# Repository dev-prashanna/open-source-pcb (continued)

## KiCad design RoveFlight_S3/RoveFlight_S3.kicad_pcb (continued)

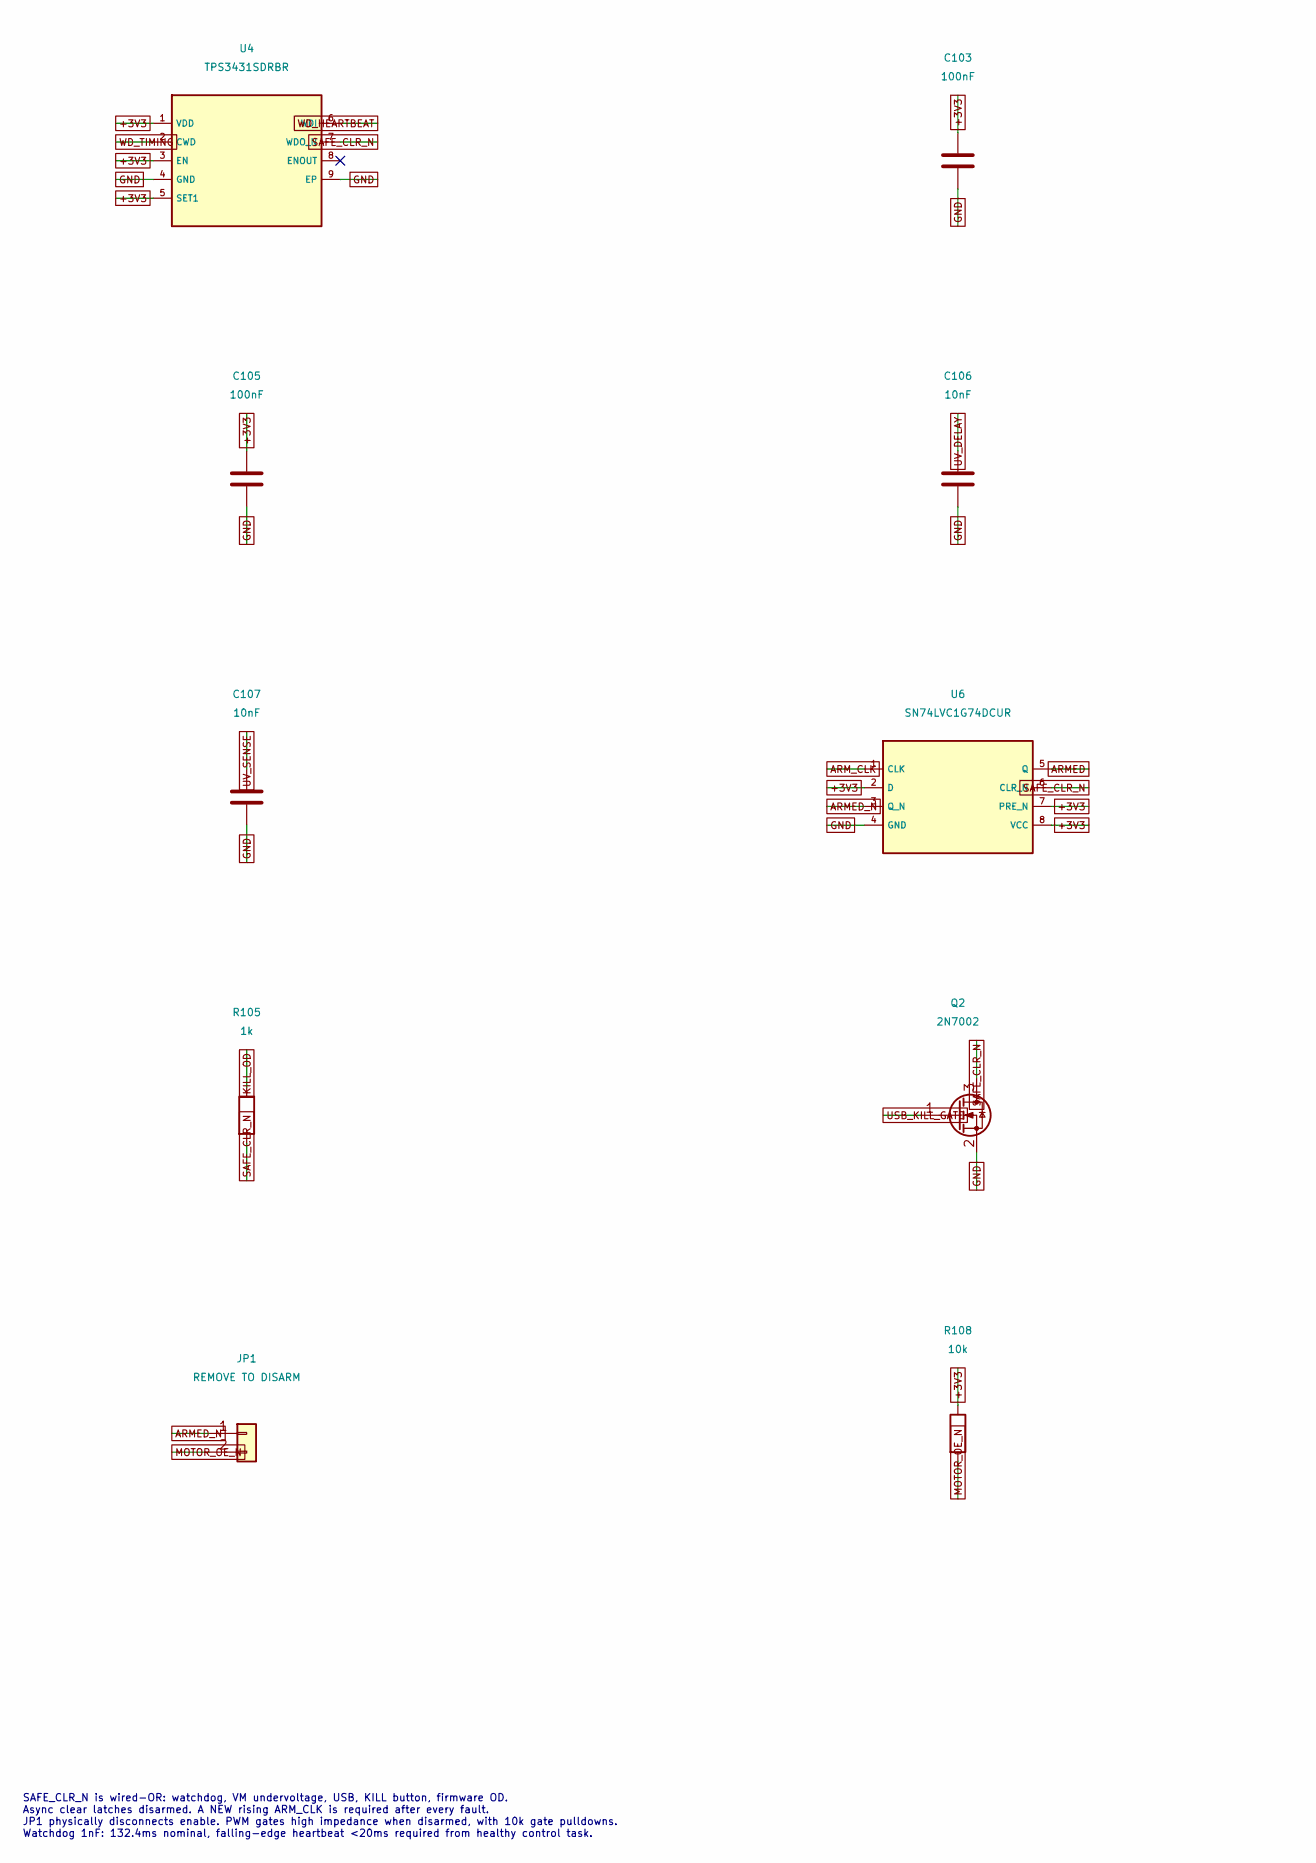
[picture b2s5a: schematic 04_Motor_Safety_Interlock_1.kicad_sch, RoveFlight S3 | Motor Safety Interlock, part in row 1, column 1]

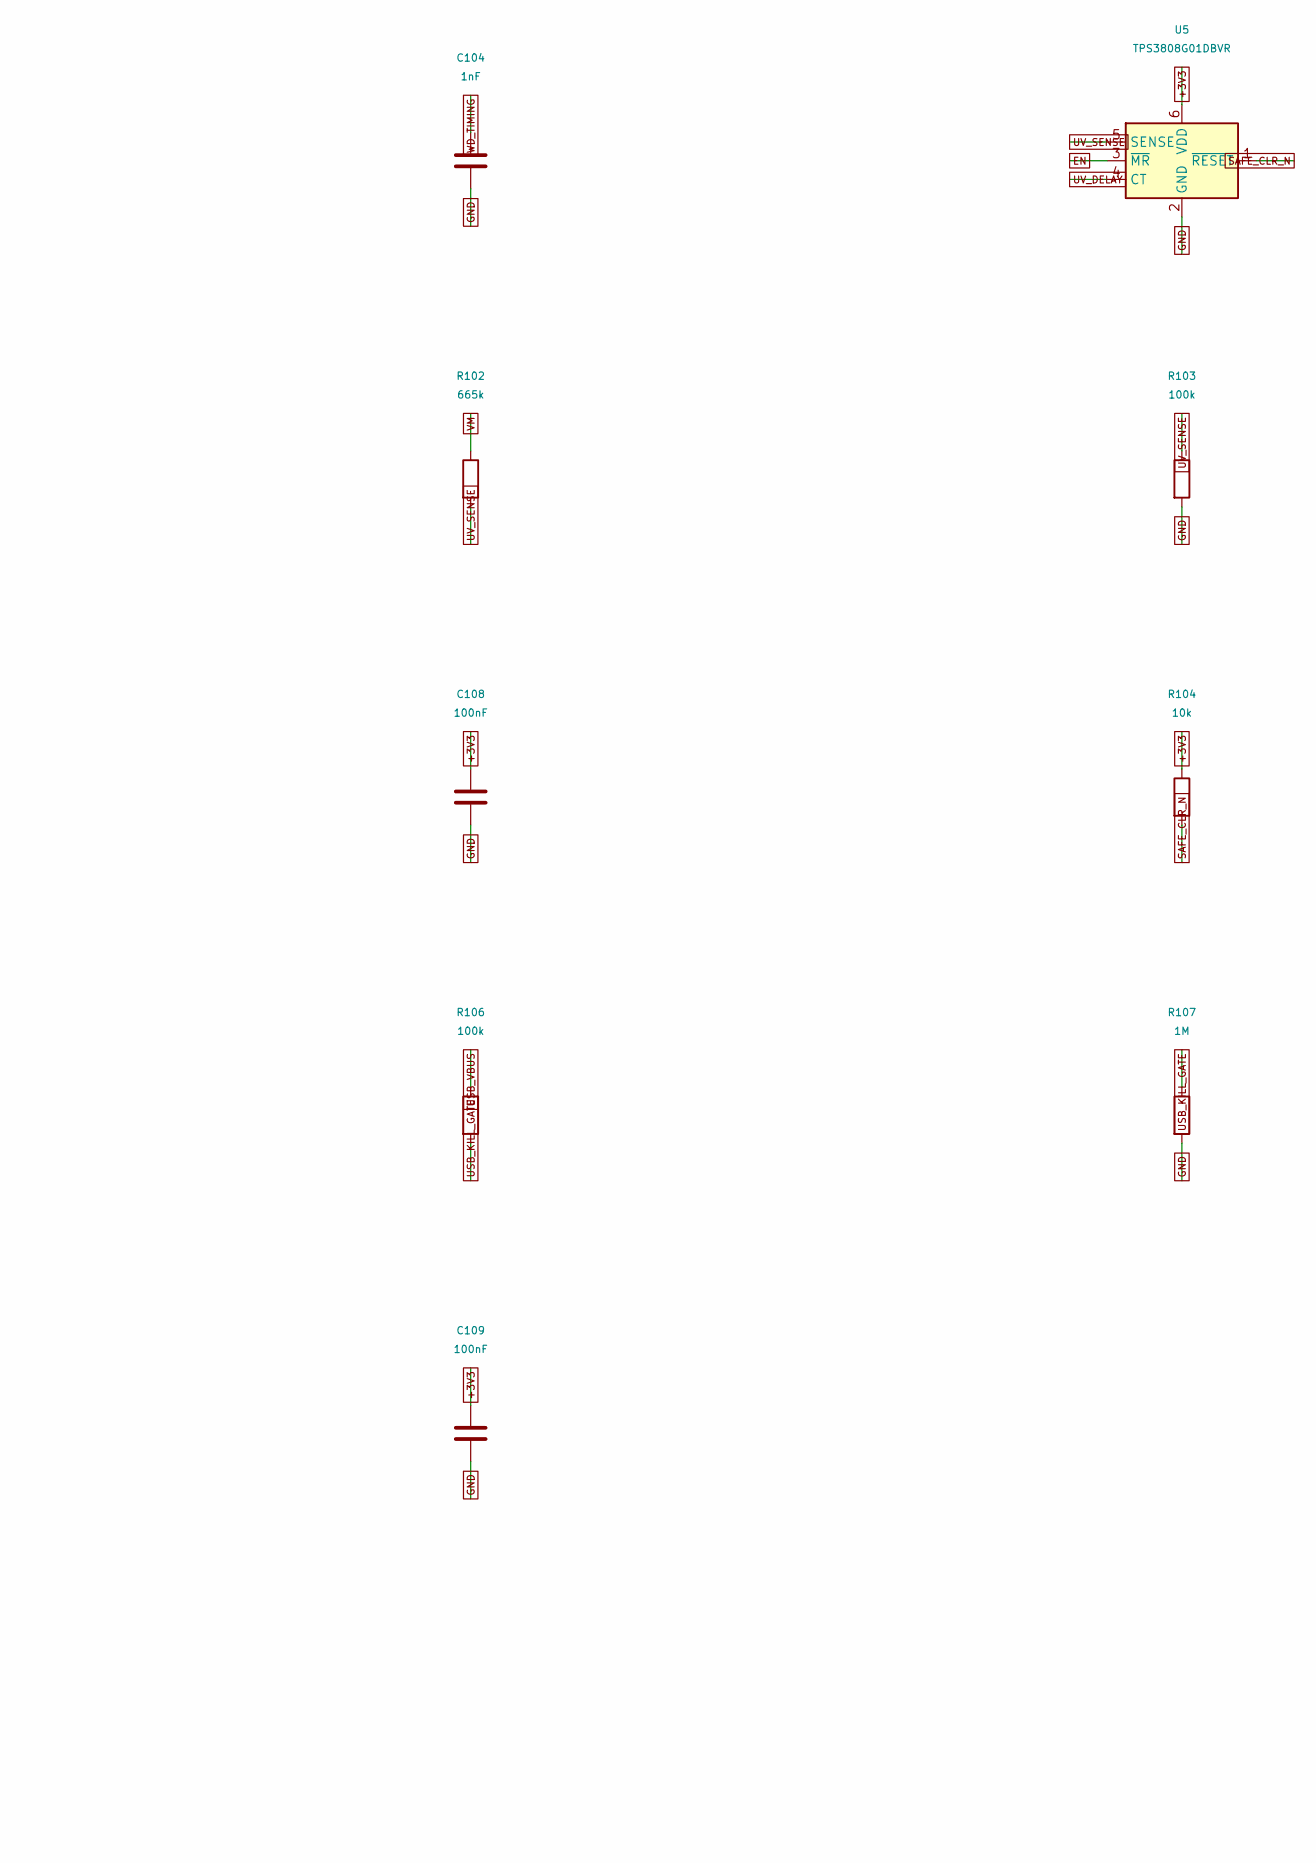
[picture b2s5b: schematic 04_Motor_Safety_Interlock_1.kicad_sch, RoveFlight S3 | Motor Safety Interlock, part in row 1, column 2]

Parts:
C103: 100nF; C_0402_1005Metric_RF_C103; MPN GRM155R71C104KA88D
C104: 1nF; C_0402_1005Metric_RF_C104; MPN GRM1555C1H102JA01D
C105: 100nF; C_0402_1005Metric_RF_C105; MPN GRM155R71C104KA88D
C106: 10nF; C_0402_1005Metric_RF_C106; MPN GRM155R71H103KA88D
C107: 10nF; C_0402_1005Metric_RF_C107; MPN GRM155R71H103KA88D
C108: 100nF; C_0402_1005Metric_RF_C108; MPN GRM155R71C104KA88D
C109: 100nF; C_0402_1005Metric_RF_C109; MPN GRM155R71C104KA88D
JP1: REMOVE TO DISARM; PinHeader_1x02_P1.27mm_Vertical; MPN 20021111-00002T4LF
Q2: 2N7002; SOT-23; MPN 2N7002
R102: 665k; R_0402_1005Metric_RF_R102; MPN RC0402FR-076653L
R103: 100k; R_0402_1005Metric_RF_R103; MPN RC0402FR-071003L
R104: 10k; R_0402_1005Metric_RF_R104; MPN RC0402FR-071002L
R105: 1k; R_0402_1005Metric_RF_R105; MPN RC0402FR-071001L
R106: 100k; R_0402_1005Metric_RF_R106; MPN RC0402FR-071003L
R107: 1M; R_0402_1005Metric_RF_R107; MPN RC0402FR-071004L
R108: 10k; R_0402_1005Metric_RF_R108; MPN RC0402FR-071002L
U4: TPS3431SDRBR; Texas_DRB0008A; MPN TPS3431SDRBR
U5: TPS3808G01DBVR; SOT-23-6; MPN TPS3808G01DBVR
U6: SN74LVC1G74DCUR; VSSOP-8_2.3x2mm_P0.5mm; MPN SN74LVC1G74DCUR

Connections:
+3V3: C103.1, C105.1, C108.1, C109.1, R104.1, R108.1, U4.1 (VDD), U4.3 (EN), U4.5 (SET1), U5.6 (VDD), U6.2 (D), U6.7 (PRE_N), U6.8 (VCC); also elsewhere on the board
ARMED: U6.5 (Q); also elsewhere on the board
ARMED_N: JP1.1, U6.3 (Q_N)
ARM_CLK: U6.1 (CLK); also elsewhere on the board
EN: U5.3 (~MR); also elsewhere on the board
GND: C103.2, C104.2, C105.2, C106.2, C107.2, C108.2, C109.2, Q2.2 (S), R103.2, R107.2, U4.4 (GND), U4.9 (EP), U5.2 (GND), U6.4 (GND); also elsewhere on the board
KILL_OD: R105.1; also elsewhere on the board
MOTOR_OE_N: JP1.2, R108.2; also elsewhere on the board
SAFE_CLR_N: Q2.3 (D), R104.2, R105.2, U4.7 (WDO_N), U5.1 (~RESET), U6.6 (CLR_N); also elsewhere on the board
USB_KILL_GATE: Q2.1 (G), R106.2, R107.1
USB_VBUS: R106.1; also elsewhere on the board
UV_DELAY: C106.1, U5.4 (CT)
UV_SENSE: C107.1, R102.2, R103.1, U5.5 (SENSE)
VM: R102.1; also elsewhere on the board
WD_HEARTBEAT: U4.6 (WDI); also elsewhere on the board
WD_TIMING: C104.1, U4.2 (CWD)

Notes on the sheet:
SAFE_CLR_N is wired-OR: watchdog, VM undervoltage, USB, KILL button, firmware OD. Async clear latches disarmed. A NEW rising ARM_CLK is required after every fault. JP1 physically disconnects enable. PWM gates high impedance when disarmed, with 10k gate pulldowns. Watchdog 1nF: 132.4ms nominal, fall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

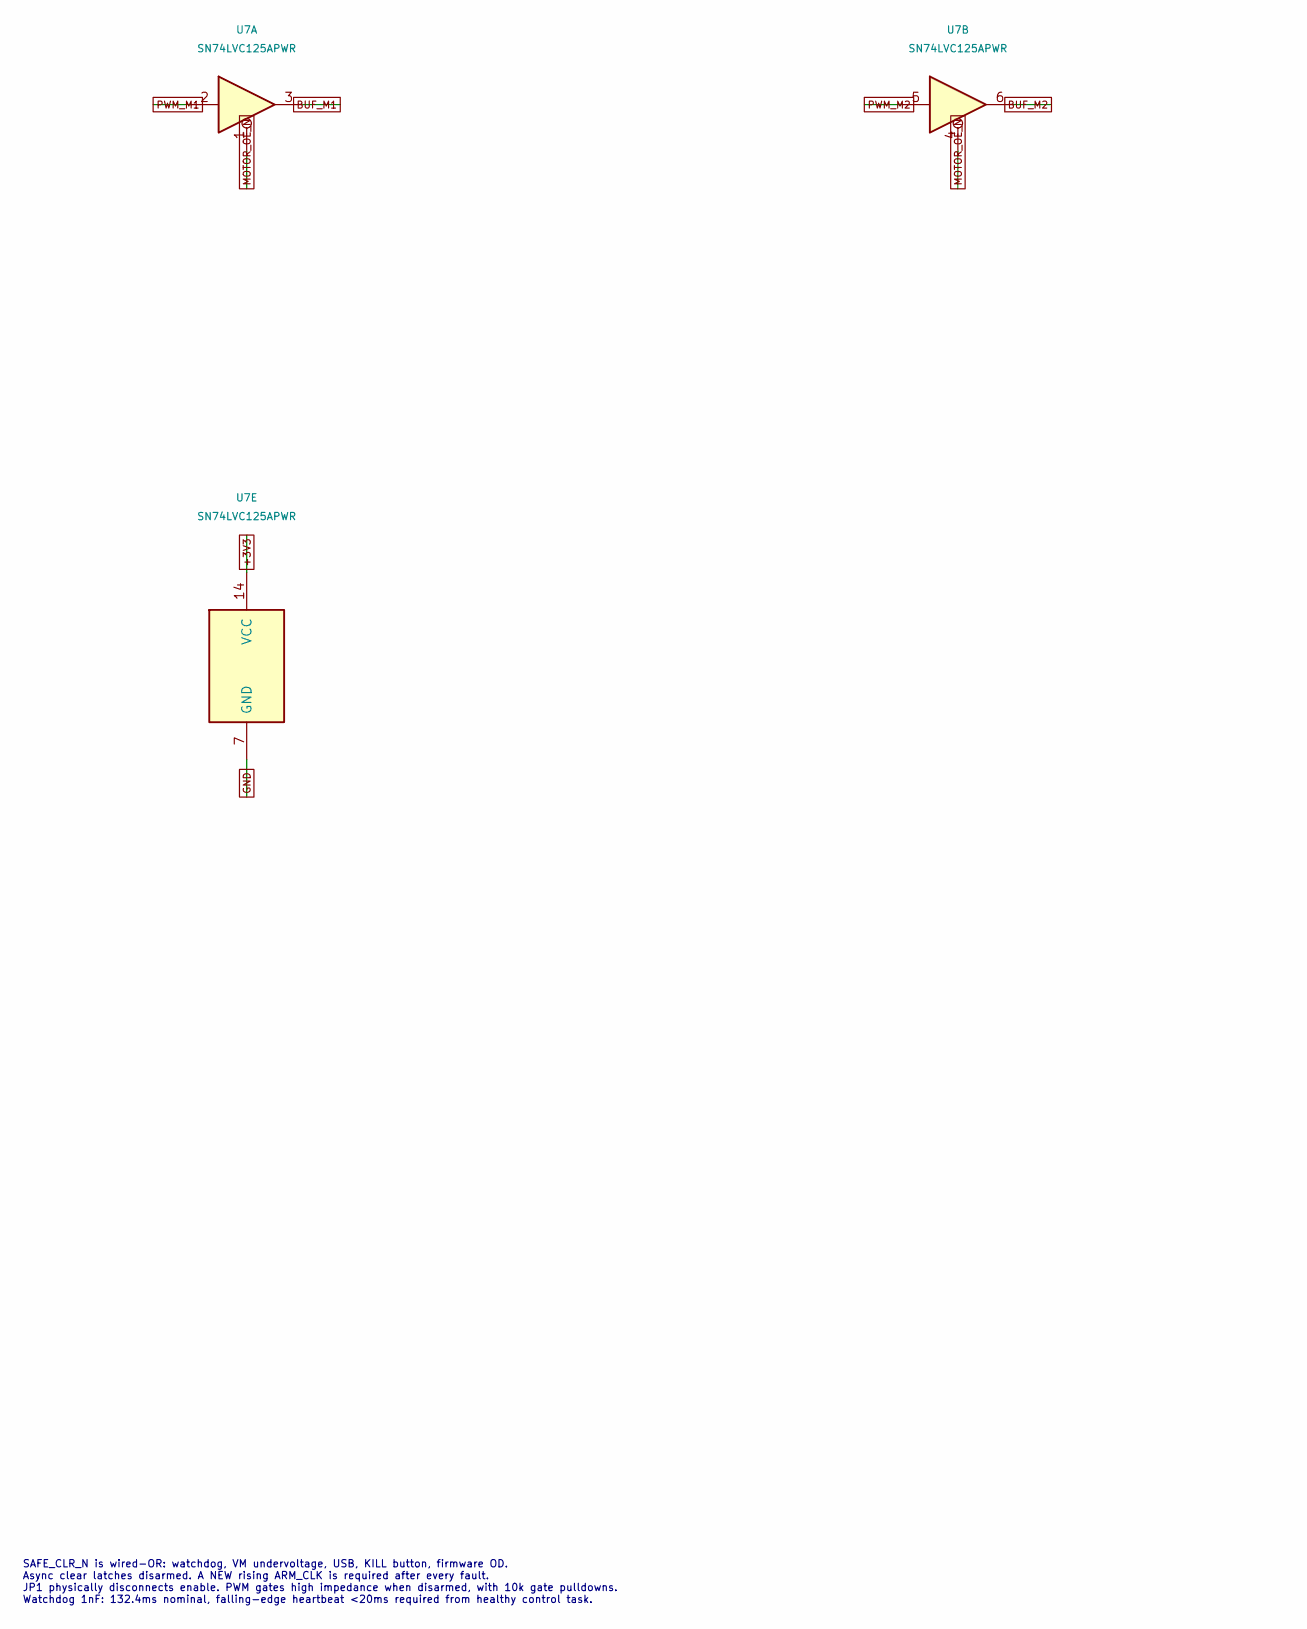
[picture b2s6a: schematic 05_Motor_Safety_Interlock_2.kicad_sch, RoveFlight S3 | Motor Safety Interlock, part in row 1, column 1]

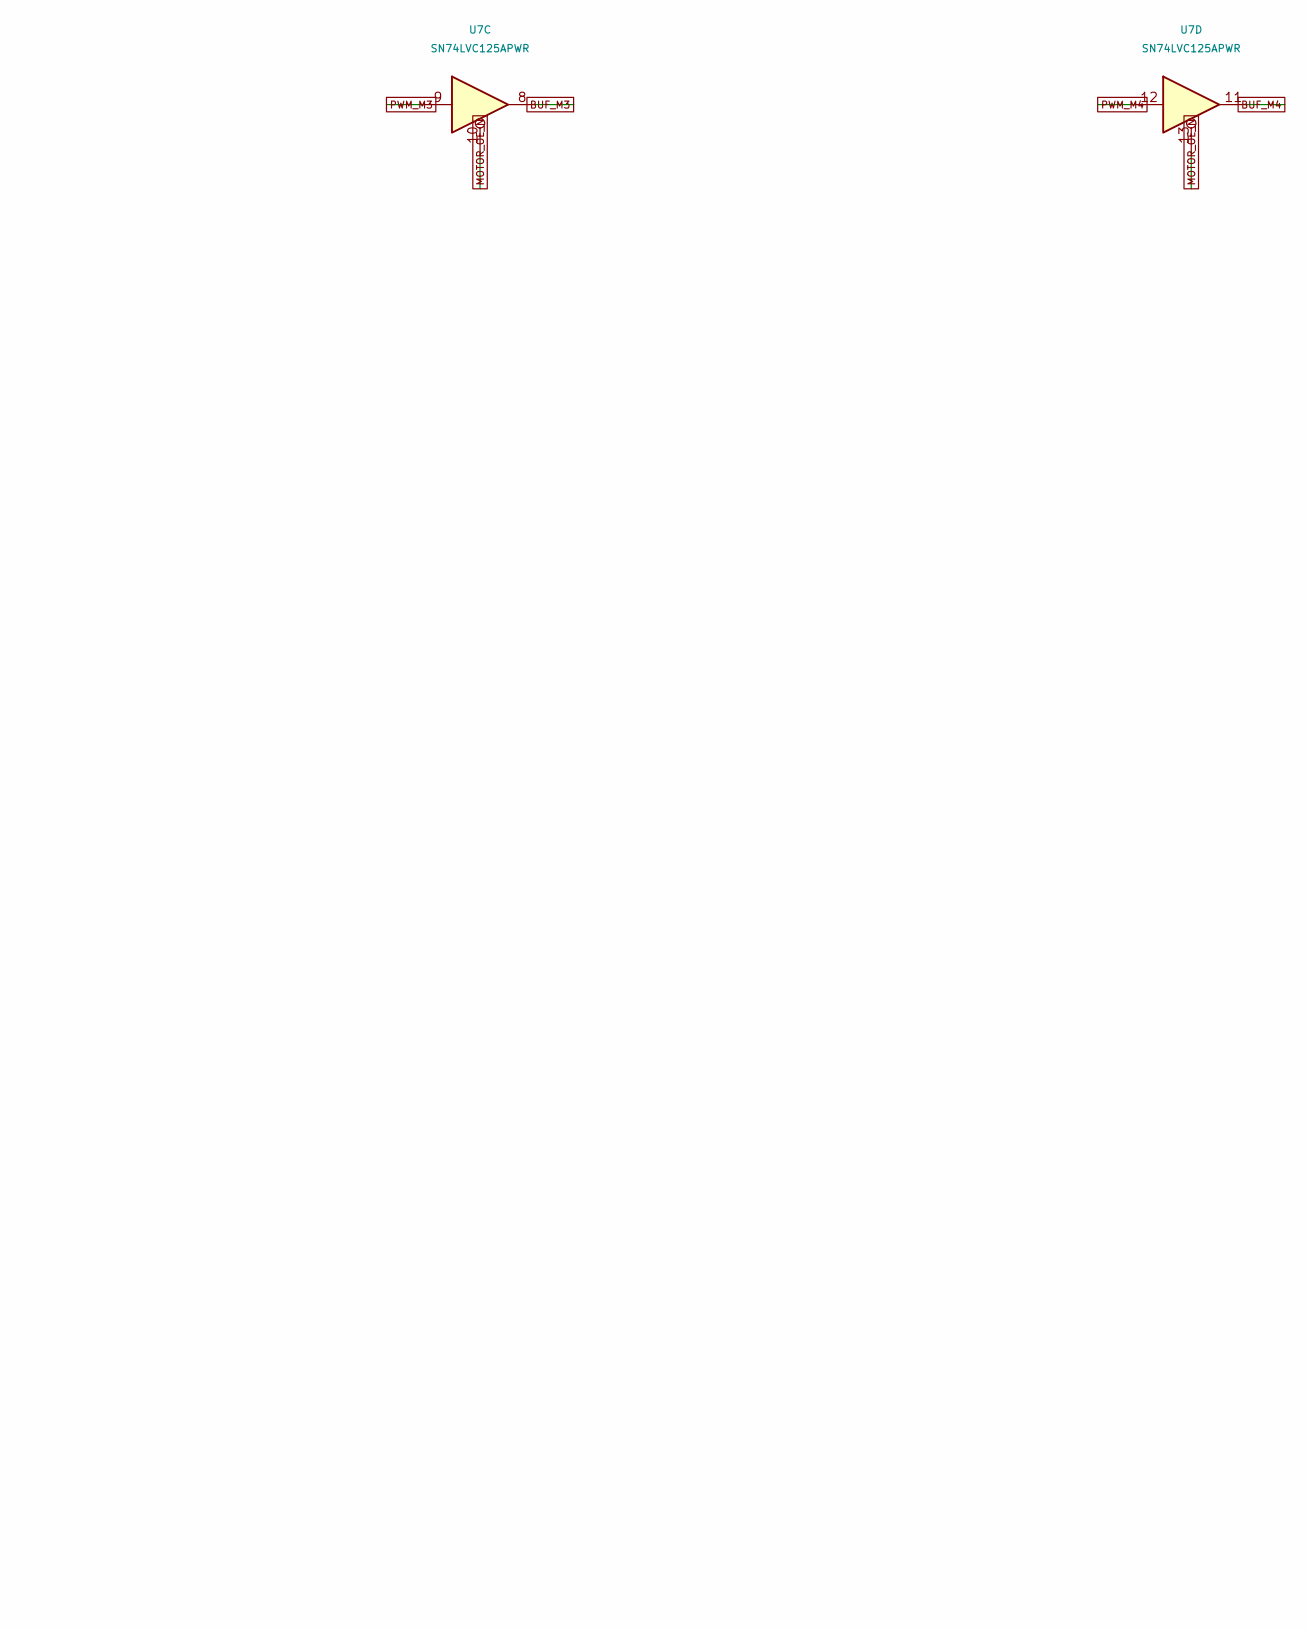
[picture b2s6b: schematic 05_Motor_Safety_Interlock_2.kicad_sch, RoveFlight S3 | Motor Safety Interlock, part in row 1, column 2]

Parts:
U7: SN74LVC125APWR; TSSOP-14_4.4x5mm_P0.65mm; MPN SN74LVC125APWR

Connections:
+3V3: U7.14 (VCC); also elsewhere on the board
BUF_M1: U7.3; also elsewhere on the board
BUF_M2: U7.6; also elsewhere on the board
BUF_M3: U7.8; also elsewhere on the board
BUF_M4: U7.11; also elsewhere on the board
GND: U7.7 (GND); also elsewhere on the board
MOTOR_OE_N: U7.1, U7.4, U7.10, U7.13; also elsewhere on the board
PWM_M1: U7.2; also elsewhere on the board
PWM_M2: U7.5; also elsewhere on the board
PWM_M3: U7.9; also elsewhere on the board
PWM_M4: U7.12; also elsewhere on the board

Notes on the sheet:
SAFE_CLR_N is wired-OR: watchdog, VM undervoltage, USB, KILL button, firmware OD. Async clear latches disarmed. A NEW rising ARM_CLK is required after every fault. JP1 physically disconnects enable. PWM gates high impedance when disarmed, with 10k gate pulldowns. Watchdog 1nF: 132.4ms nominal, fall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

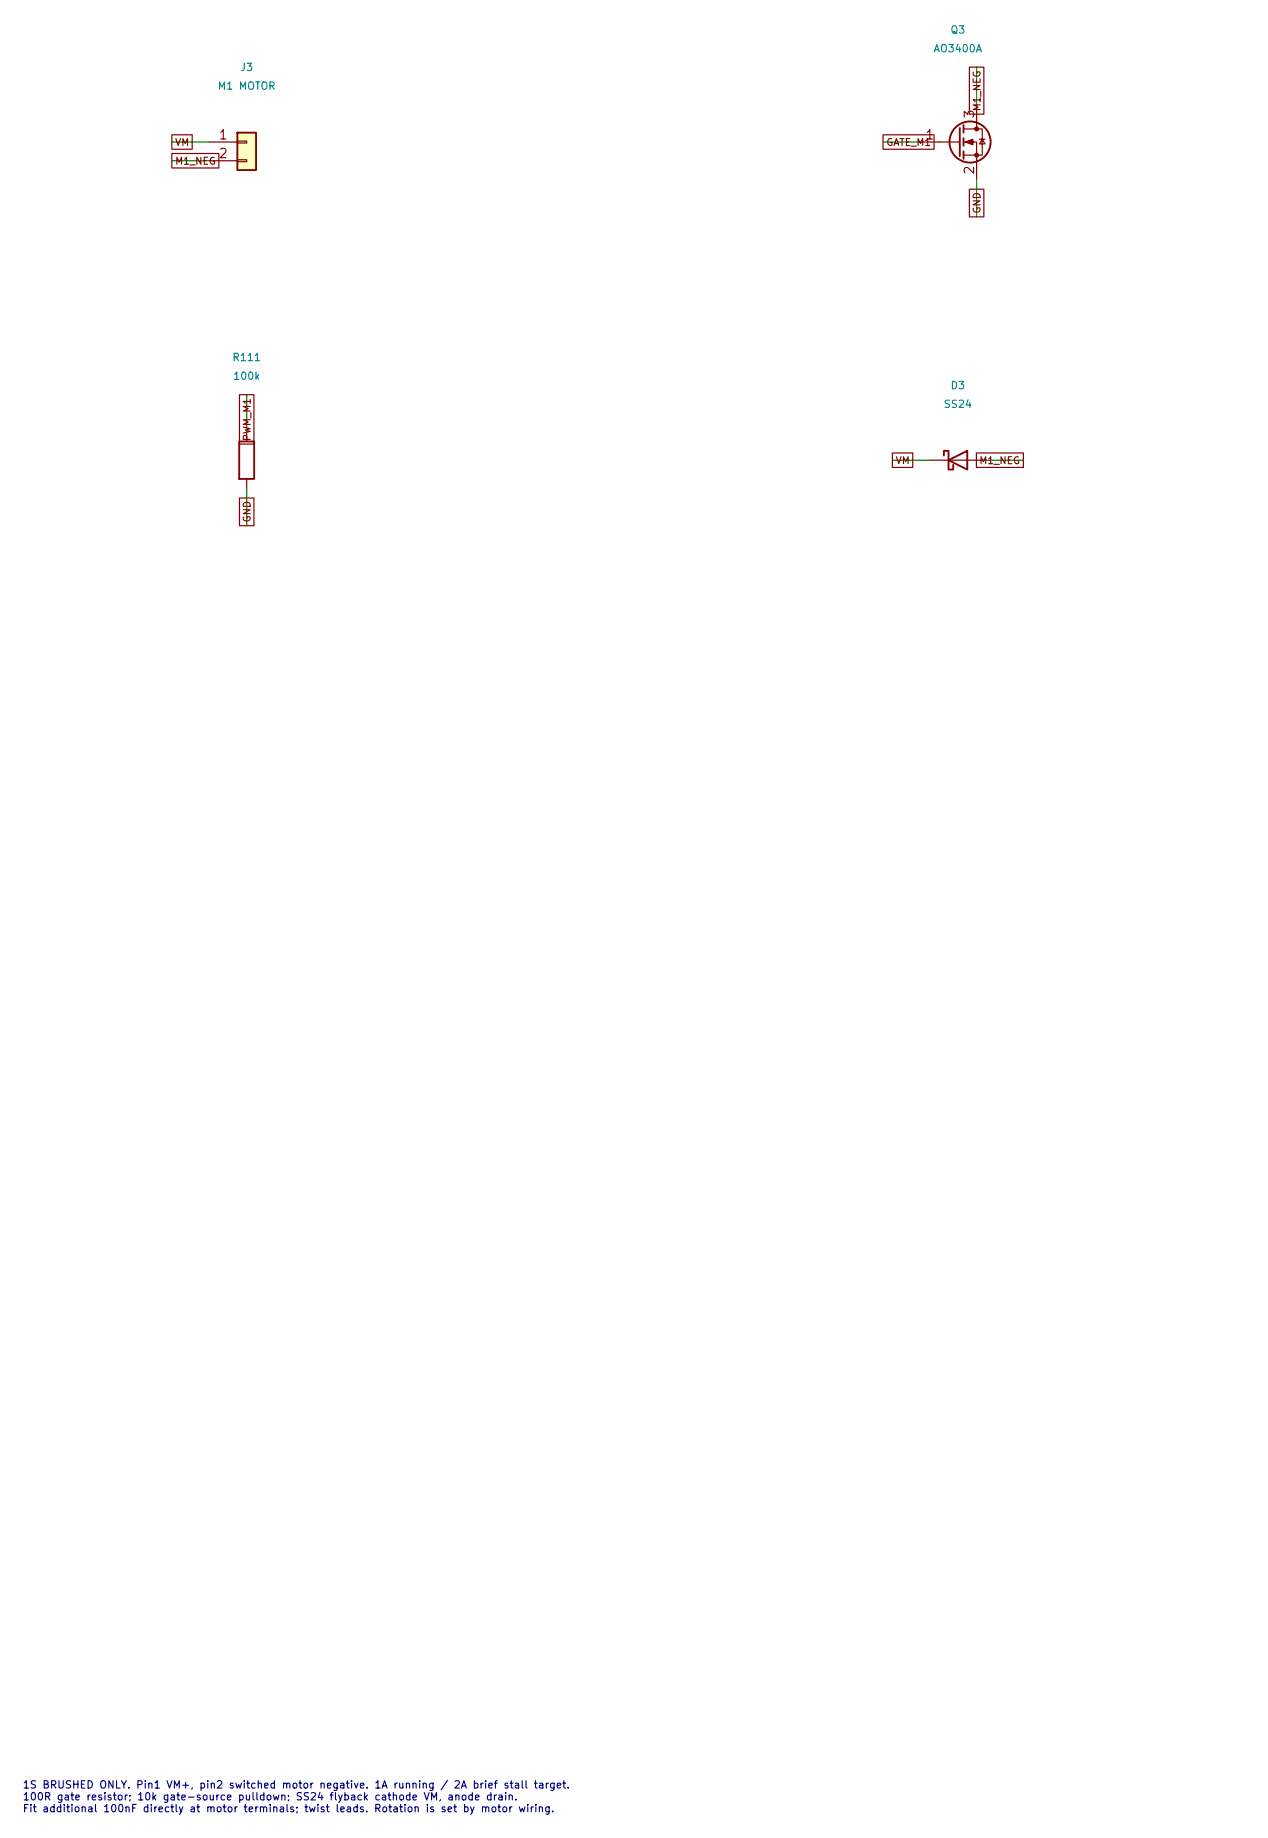
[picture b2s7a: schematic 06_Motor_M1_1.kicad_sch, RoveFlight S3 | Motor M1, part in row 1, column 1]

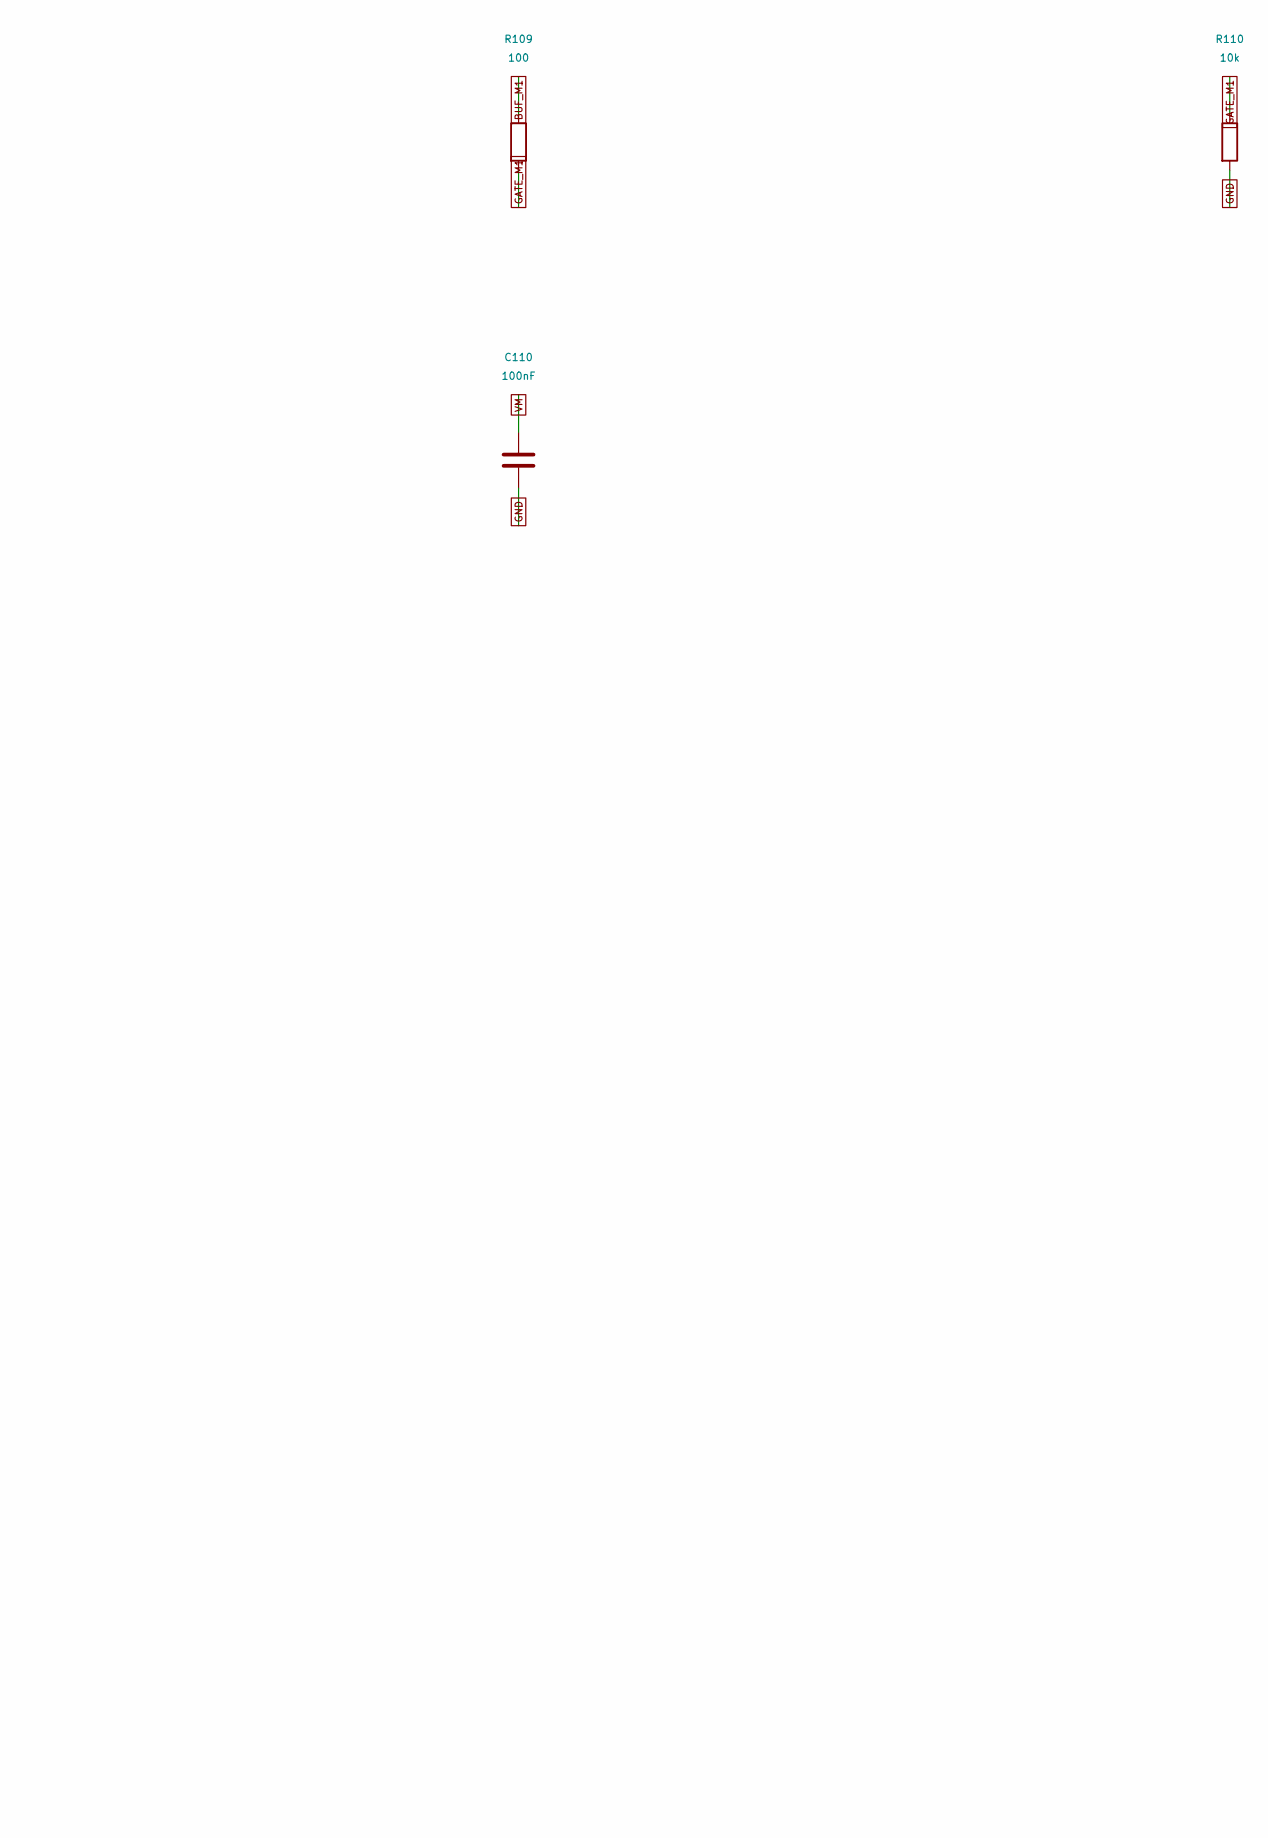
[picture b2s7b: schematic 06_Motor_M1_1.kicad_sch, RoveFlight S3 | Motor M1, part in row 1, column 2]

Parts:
C110: 100nF; C_0402_1005Metric_RF_C110; MPN GRM155R71C104KA88D
D3: SS24; D_SMA; MPN SS24-13-F
J3: M1 MOTOR; MotorPads; MPN PCB_SOLDER_PADS_24AWG
Q3: AO3400A; SOT-23; MPN AO3400A
R109: 100; R_0402_1005Metric_RF_R109; MPN RC0402FR-071000L
R110: 10k; R_0402_1005Metric_RF_R110; MPN RC0402FR-071002L
R111: 100k; R_0402_1005Metric_RF_R111; MPN RC0402FR-071003L

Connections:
BUF_M1: R109.1; also elsewhere on the board
GATE_M1: Q3.1 (G), R109.2, R110.1
GND: C110.2, Q3.2 (S), R110.2, R111.2; also elsewhere on the board
M1_NEG: D3.2 (A), J3.2, Q3.3 (D)
PWM_M1: R111.1; also elsewhere on the board
VM: C110.1, D3.1 (K), J3.1; also elsewhere on the board

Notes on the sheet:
1S BRUSHED ONLY. Pin1 VM+, pin2 switched motor negative. 1A running / 2A brief stall target. 100R gate resistor; 10k gate-source pulldown; SS24 flyback cathode VM, anode drain. Fit additional 100nF directly at motor terminals; twist leads. Rotation is set by motor wiring.

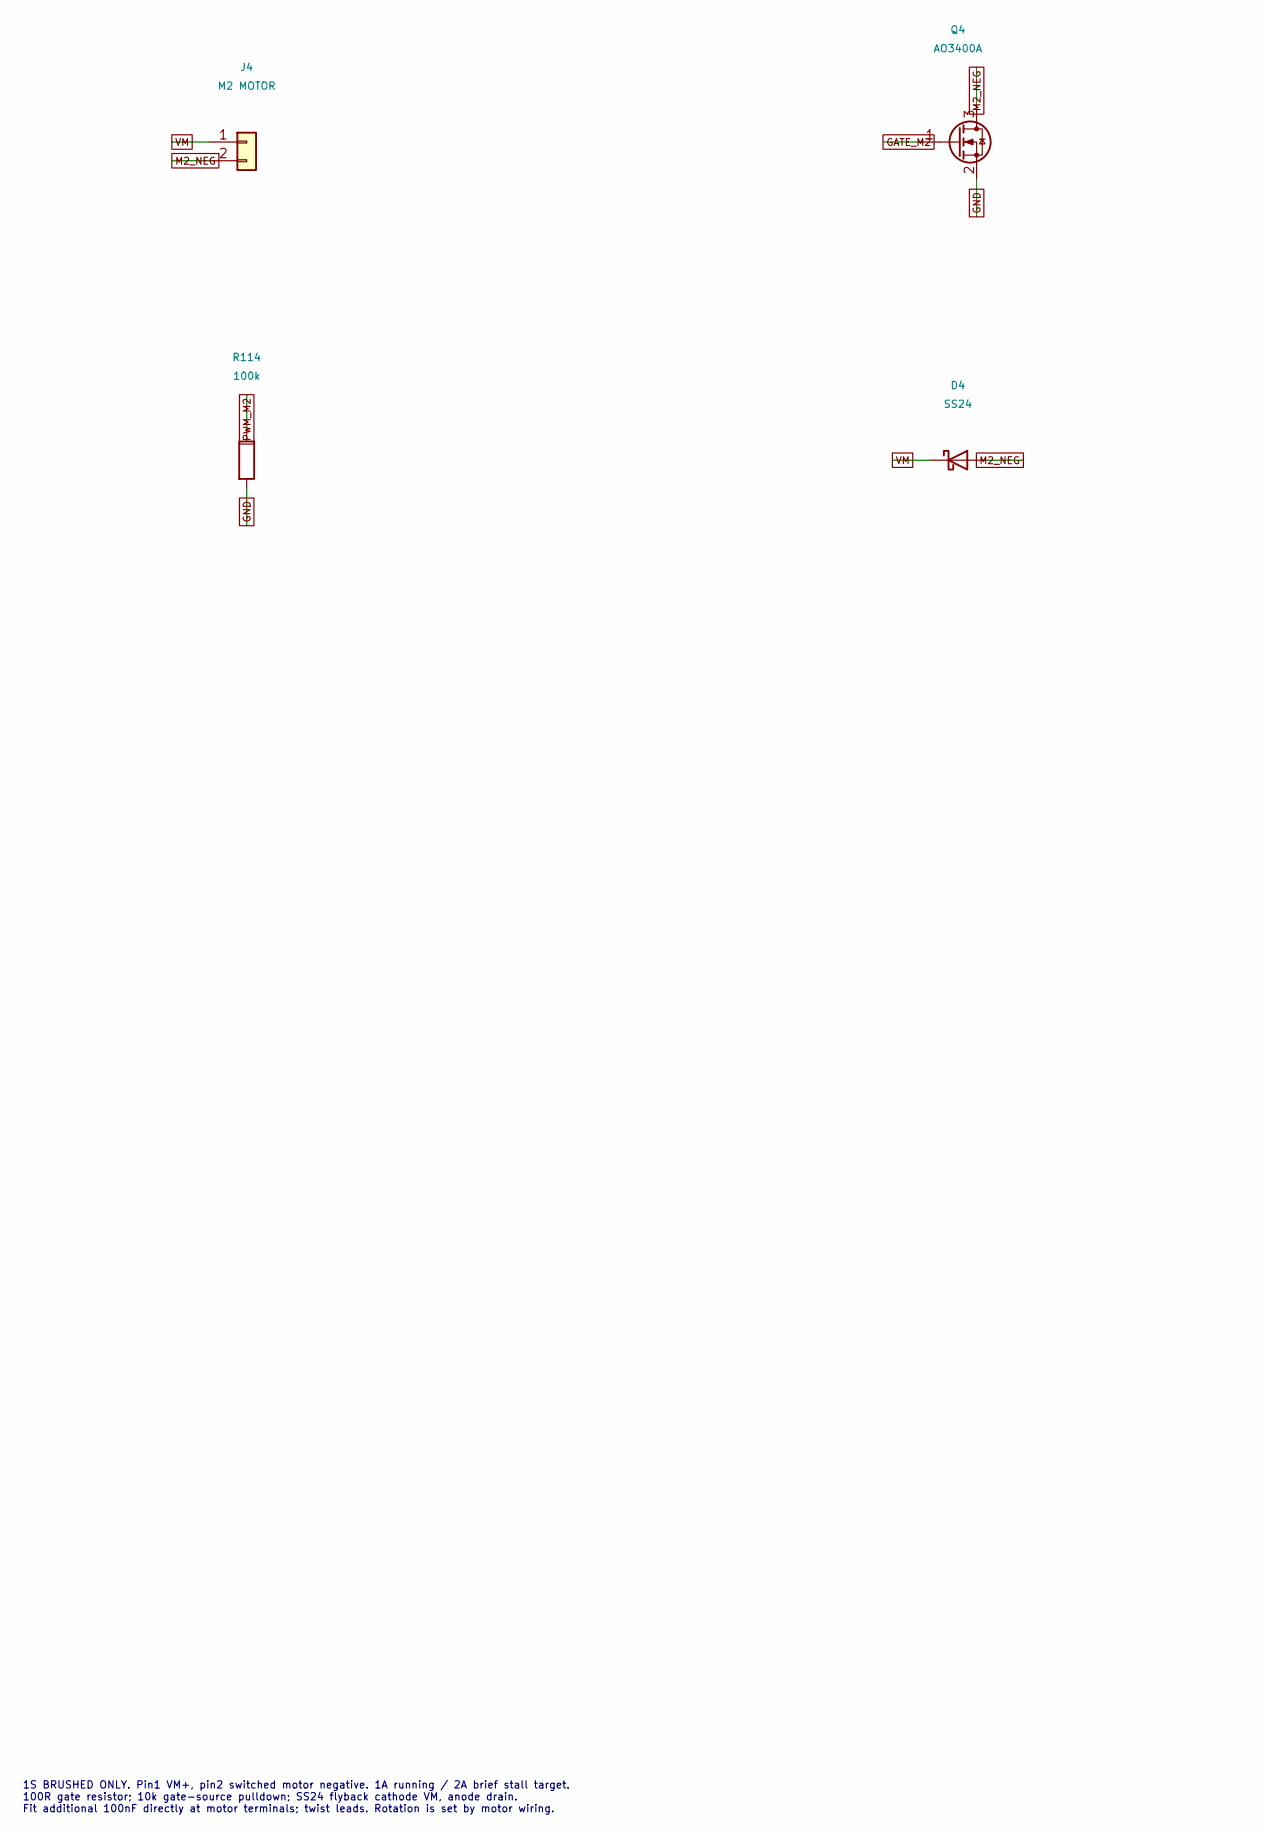
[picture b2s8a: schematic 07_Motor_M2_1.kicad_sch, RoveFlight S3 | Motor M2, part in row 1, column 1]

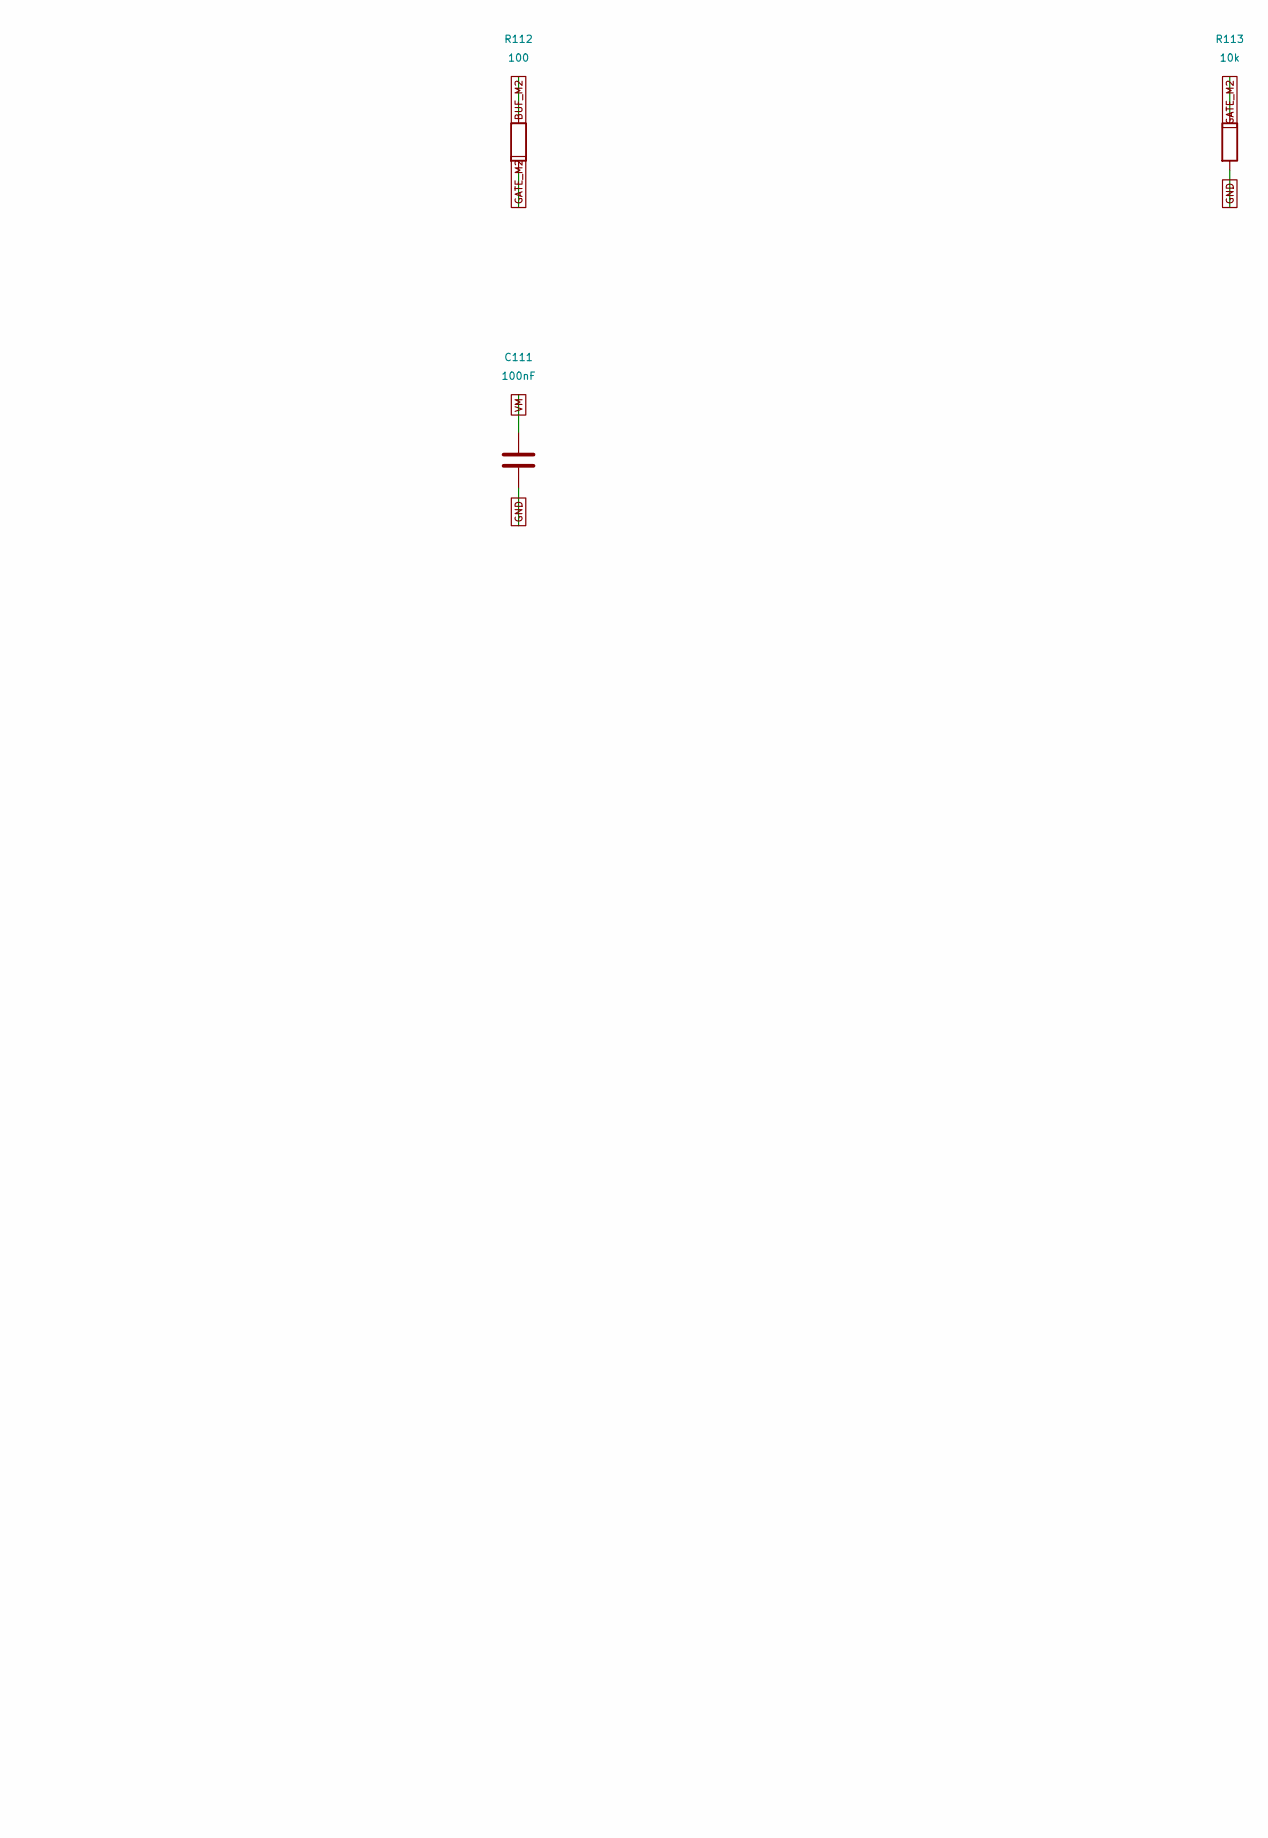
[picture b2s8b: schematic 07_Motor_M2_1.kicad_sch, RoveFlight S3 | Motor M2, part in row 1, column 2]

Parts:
C111: 100nF; C_0402_1005Metric_RF_C111; MPN GRM155R71C104KA88D
D4: SS24; D_SMA; MPN SS24-13-F
J4: M2 MOTOR; MotorPads; MPN PCB_SOLDER_PADS_24AWG
Q4: AO3400A; SOT-23; MPN AO3400A
R112: 100; R_0402_1005Metric_RF_R112; MPN RC0402FR-071000L
R113: 10k; R_0402_1005Metric_RF_R113; MPN RC0402FR-071002L
R114: 100k; R_0402_1005Metric_RF_R114; MPN RC0402FR-071003L

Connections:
BUF_M2: R112.1; also elsewhere on the board
GATE_M2: Q4.1 (G), R112.2, R113.1
GND: C111.2, Q4.2 (S), R113.2, R114.2; also elsewhere on the board
M2_NEG: D4.2 (A), J4.2, Q4.3 (D)
PWM_M2: R114.1; also elsewhere on the board
VM: C111.1, D4.1 (K), J4.1; also elsewhere on the board

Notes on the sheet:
1S BRUSHED ONLY. Pin1 VM+, pin2 switched motor negative. 1A running / 2A brief stall target. 100R gate resistor; 10k gate-source pulldown; SS24 flyback cathode VM, anode drain. Fit additional 100nF directly at motor terminals; twist leads. Rotation is set by motor wiring.

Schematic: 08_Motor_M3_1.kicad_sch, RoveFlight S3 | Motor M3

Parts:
C112: 100nF; C_0402_1005Metric_RF_C112; MPN GRM155R71C104KA88D
D5: SS24; D_SMA; MPN SS24-13-F
J5: M3 MOTOR; MotorPads; MPN PCB_SOLDER_PADS_24AWG
Q5: AO3400A; SOT-23; MPN AO3400A
R115: 100; R_0402_1005Metric_RF_R115; MPN RC0402FR-071000L
R116: 10k; R_0402_1005Metric_RF_R116; MPN RC0402FR-071002L
R117: 100k; R_0402_1005Metric_RF_R117; MPN RC0402FR-071003L

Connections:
BUF_M3: R115.1; also elsewhere on the board
GATE_M3: Q5.1 (G), R115.2, R116.1
GND: C112.2, Q5.2 (S), R116.2, R117.2; also elsewhere on the board
M3_NEG: D5.2 (A), J5.2, Q5.3 (D)
PWM_M3: R117.1; also elsewhere on the board
VM: C112.1, D5.1 (K), J5.1; also elsewhere on the board

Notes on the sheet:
1S BRUSHED ONLY. Pin1 VM+, pin2 switched motor negative. 1A running / 2A brief stall target. 100R gate resistor; 10k gate-source pulldown; SS24 flyback cathode VM, anode drain. Fit additional 100nF directly at motor terminals; twist leads. Rotation is set by motor wiring.

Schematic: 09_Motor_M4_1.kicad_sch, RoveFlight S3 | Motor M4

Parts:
C113: 100nF; C_0402_1005Metric_RF_C113; MPN GRM155R71C104KA88D
D6: SS24; D_SMA; MPN SS24-13-F
J6: M4 MOTOR; MotorPads; MPN PCB_SOLDER_PADS_24AWG
Q6: AO3400A; SOT-23; MPN AO3400A
R118: 100; R_0402_1005Metric_RF_R118; MPN RC0402FR-071000L
R119: 10k; R_0402_1005Metric_RF_R119; MPN RC0402FR-071002L
R120: 100k; R_0402_1005Metric_RF_R120; MPN RC0402FR-071003L

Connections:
BUF_M4: R118.1; also elsewhere on the board
GATE_M4: Q6.1 (G), R118.2, R119.1
GND: C113.2, Q6.2 (S), R119.2, R120.2; also elsewhere on the board
M4_NEG: D6.2 (A), J6.2, Q6.3 (D)
PWM_M4: R120.1; also elsewhere on the board
VM: C113.1, D6.1 (K), J6.1; also elsewhere on the board

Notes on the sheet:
1S BRUSHED ONLY. Pin1 VM+, pin2 switched motor negative. 1A running / 2A brief stall target. 100R gate resistor; 10k gate-source pulldown; SS24 flyback cathode VM, anode drain. Fit additional 100nF directly at motor terminals; twist leads. Rotation is set by motor wiring.
